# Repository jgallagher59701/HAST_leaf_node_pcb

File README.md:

# HAST leaf node pcb files

The first PCB used EagleCAD, but I've switched to KiCAD. Version 0.5 is the current version of the PCB in used as of Nov. 2021.

Supportted by a grant from ESIP.

Contact: jgallagher@opendap.org

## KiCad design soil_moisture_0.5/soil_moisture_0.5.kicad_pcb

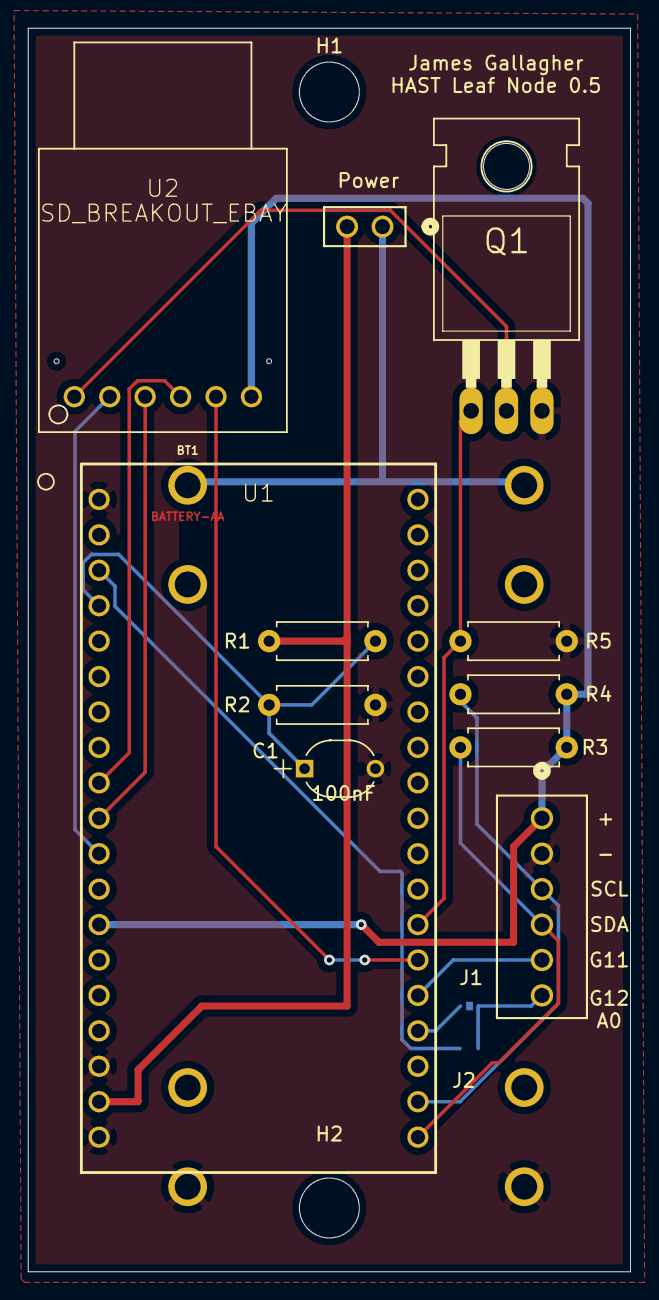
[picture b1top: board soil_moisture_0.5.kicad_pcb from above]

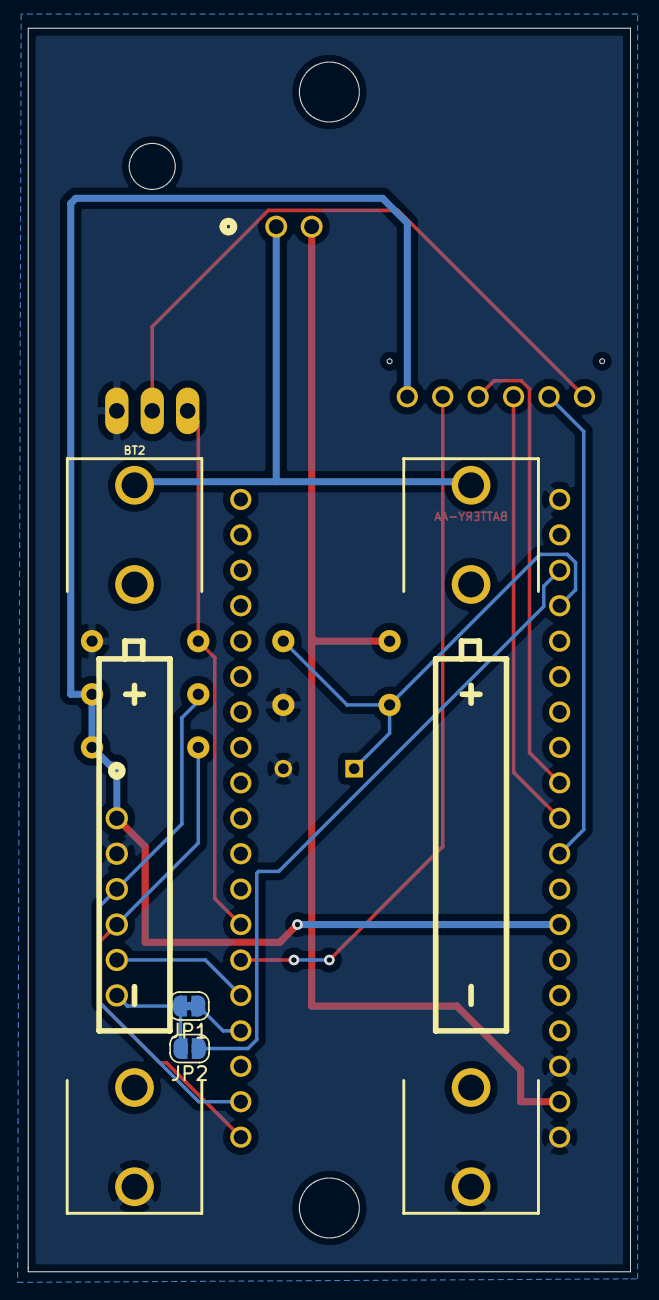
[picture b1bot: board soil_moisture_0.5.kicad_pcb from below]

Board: 2 copper layers, 43.2 x 89.2 mm, 17 parts (4 on the bottom side), 17 nets.

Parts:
BT1, BT2: BATTERY-AA; BATTERY-AA-KIT
C1: 100nF; C322C104K5R5TA
H1, H2: MountingHole; MountingHole_4.3mm_M4
J1: PPTC021LFBN-RC; CONN2_LFBN-RC_SUL
J2: 1725698; CONN_1725698_PXC
JP1: SolderJumper_2_Bridged; SolderJumper-2_P1.3mm_Bridged_RoundedPad1.0x1.5mm
JP2: SolderJumper_2_Open; SolderJumper-2_P1.3mm_Open_RoundedPad1.0x1.5mm
Q1: FDP7030BL; TO220
R1, R2: 1M; R_Axial_DIN0207_L6.3mm_D2.5mm_P7.62mm_Horizontal
R3, R4, R5: 10k; R_Axial_DIN0207_L6.3mm_D2.5mm_P7.62mm_Horizontal
U1: RS_MINI_ULTRA_PRO_V3; RS_MINI_ULTRA_PRO_V2
U2: SD_BREAKOUT_EBAY

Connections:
3V3: J2.1, R3.2, R4.2, U1.13, U2.3V3
A0: JP2.1, U1.3
BAT: J1.2, R1.1, U1.18
GND: BT1.GND@1, BT2.GND@1, C1.2, J2.2, Q1.3, R2.2, R5.2, U1.1, U1.17, U1.19
GPIO11: J2.5, U1.24
GPIO12: JP1.1, U1.23
MISO: U1.11, U2.MISO
MOSI: U1.9, U2.MOSI
unnamed: BT1.PWR@1, BT2.PWR@1, J1.1
unnamed: C1.1, R1.2, R2.1, U1.4
unnamed: J2.6, JP1.2, JP2.2
unnamed: Q1.1, R5.1, U1.26
unnamed: Q1.2, U2.GND
SCK: U1.10, U2.CLK
SCL: J2.3, R4.1, U1.21
SDA: J2.4, R3.1, U1.20
SS: U1.25, U2.CS

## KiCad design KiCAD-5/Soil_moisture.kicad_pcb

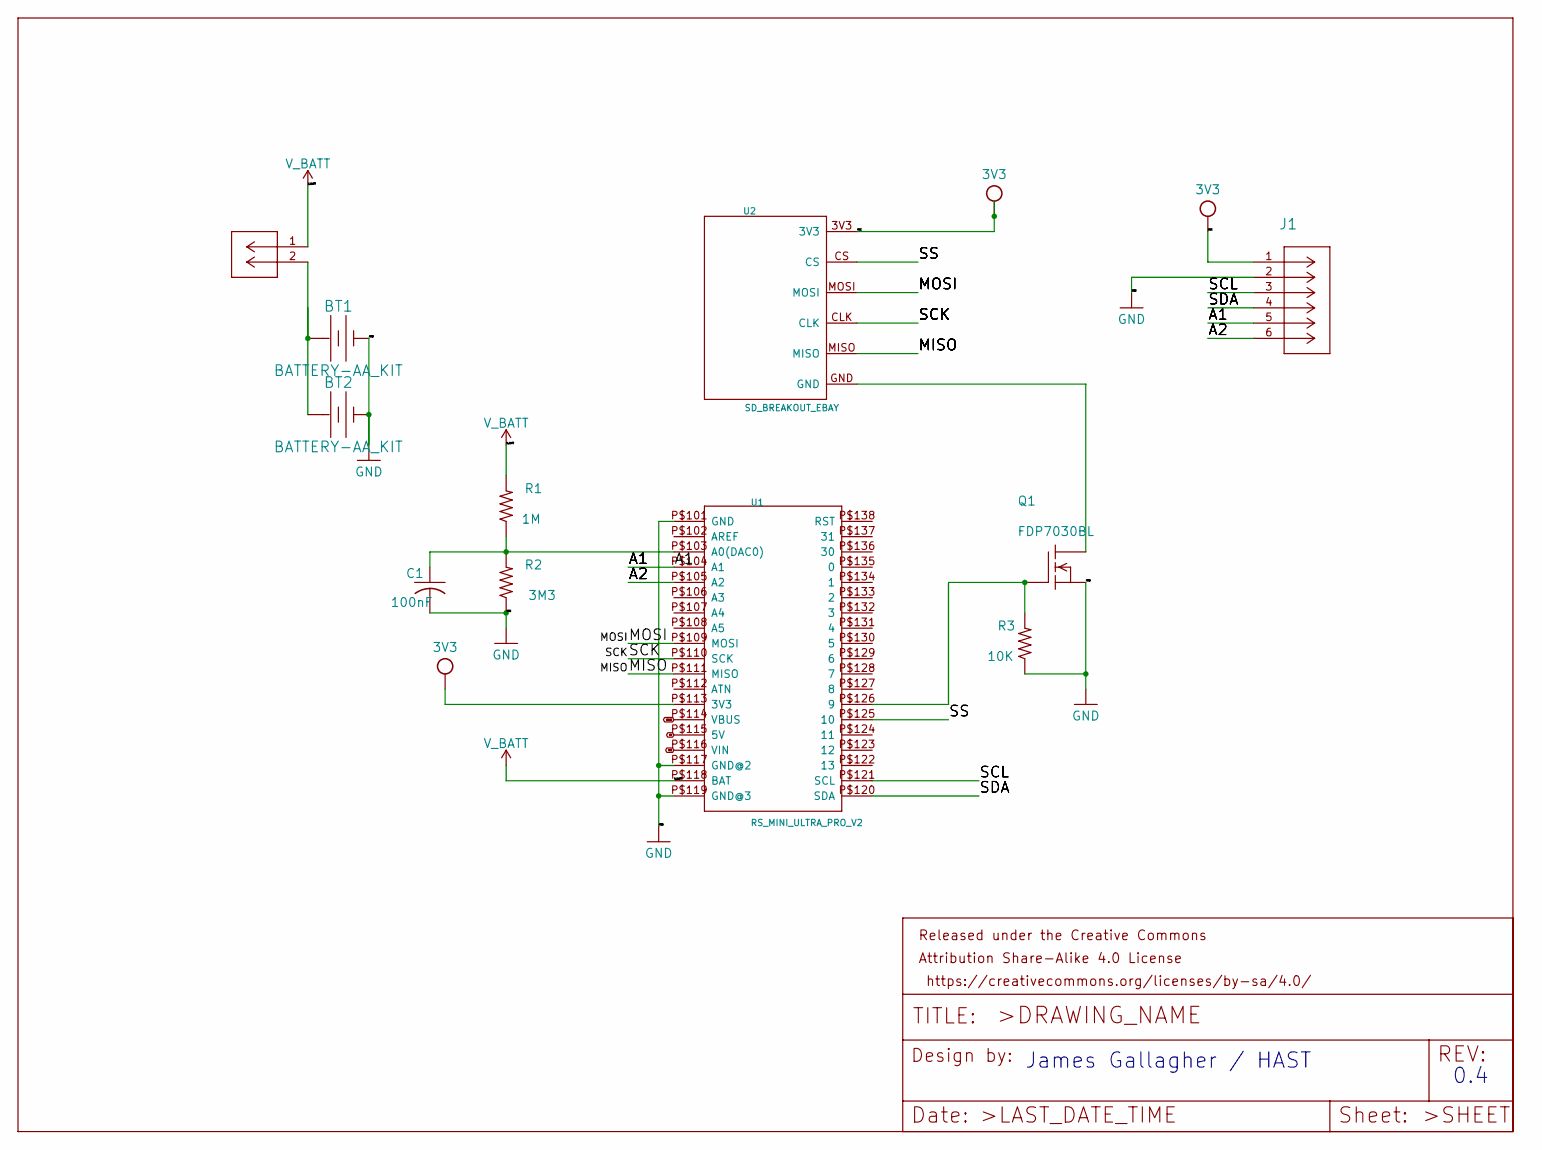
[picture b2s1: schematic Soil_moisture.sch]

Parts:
BAT_GND1: PPTC021LFBN-RC; CONN2_LFBN-RC_SUL
BT1, BT2: BATTERY-AA_KIT; BATTERY-AA-KIT
C1: 100nF; C050-035X075
FRAME1: FRAME-LETTER; CREATIVE_COMMONS
J1: 1725698; CONN_1725698_PXC
Q1: FDP7030BL; TO220
R1: 1M; 0309_10
R2: 3M3; 0309_10
R3: 10K; 0309_10
U1: RS_MINI_ULTRA_PRO_V2
U2: SD_BREAKOUT_EBAY

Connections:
5V: U1.P$115 (5V)
/A1: J1.5, U1.P$104 (A1)
/A2: J1.6, U1.P$105 (A2)
/MISO: U1.P$111 (MISO), U2.MISO
/MOSI: U1.P$109 (MOSI), U2.MOSI
/SCK: U1.P$110 (SCK), U2.CLK
/SCL: J1.3, U1.P$121 (SCL)
/SDA: J1.4, U1.P$120 (SDA)
/SS: U1.P$125 (10), U2.CS
GND: BT1.GND@1 (-), BT2.GND@1 (-), C1.2, J1.2, Q1.3 (S), R2.1, R3.1, U1.P$101 (GND), U1.P$117 (GND@2), U1.P$119 (GND@3)
unnamed: BAT_GND1.2, BT1.PWR@1 (+), BT2.PWR@1 (+)
unnamed: C1.1, R1.1, R2.2, U1.P$103 (A0(DAC0))
unnamed: Q1.1 (G), R3.2, U1.P$126 (9)
unnamed: Q1.2 (D), U2.GND
VBUS: U1.P$114 (VBUS)
VCC: J1.1, U1.P$113 (3V3), U2.3V3
VIN: U1.P$116 (VIN)
V_BATT: BAT_GND1.1, R1.2, U1.P$118 (BAT)

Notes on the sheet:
James Gallagher / HAST
0.4

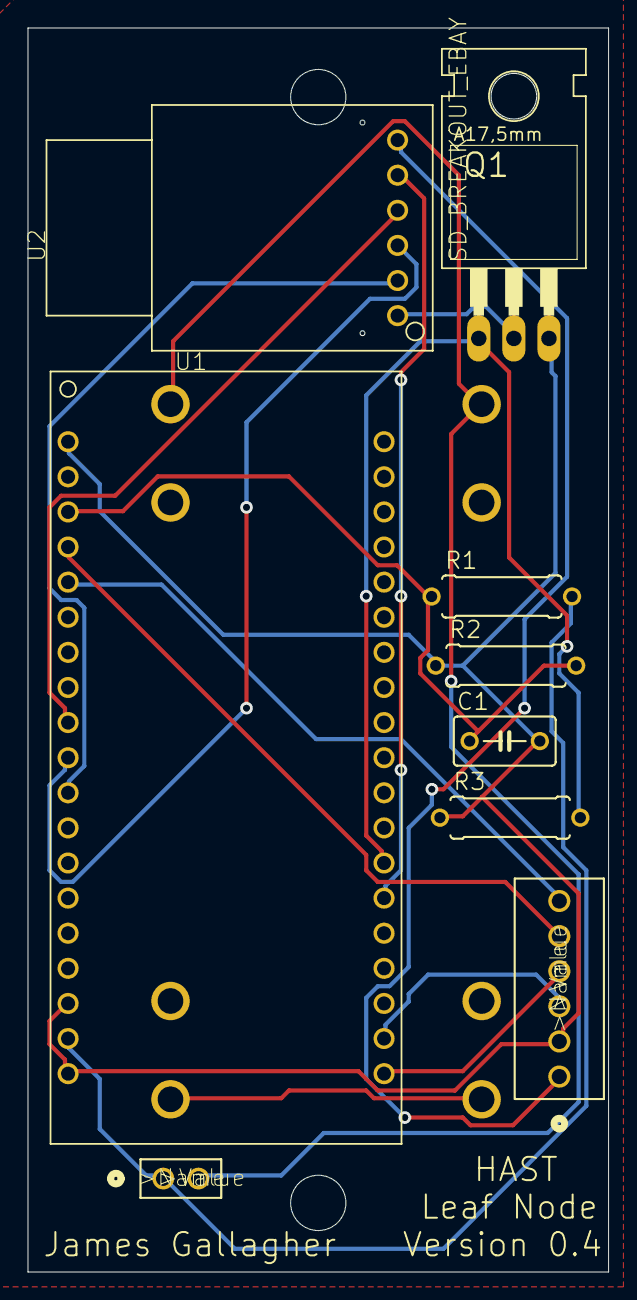
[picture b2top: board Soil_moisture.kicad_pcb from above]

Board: 2 copper layers, 42.0 x 90.0 mm, 14 parts (0 on the bottom side), 15 nets.

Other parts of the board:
@HOLE0, @HOLE1: (no value)

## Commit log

2021-03-10 Imported Eagle schematic to KiCAD, added the result here.
2021-03-10 Added a note about KiCAD 5 to the README
2021-08-27 PCB version 0.5 - now with 3D models
2021-08-28 Various hacks - added jumpers for GPIO/A0
2021-09-07 Added second voltage divider for Vbat; board outline
2021-09-09 Added Gerbers and a BOM
2021-09-13 BOM updates
2021-10-01 Added a PDF of the schematic
2021-10-01 At the office, KiCAD is using newer libraries.
    This is an update based on those newer libraries. I may
    have to update KiCAD at home to use the files on this branch.
    Test, merge if possible.
2021-11-18 Cache update
    Not sure this should be in git, but it is...

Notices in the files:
soil_moisture_0.5/soil_moisture_0.5.kicad_pcb:
License: CC BY 4.0
parts and their libraries:
https://creativecommons.org/licenses/by-sa/4.0
Released under the Creative Commons Attribution Share-Alike 4.0 License
my_library: COPYRIGHT: Copyright (C) 2018 Accelerated Designs. All rights reserved
SparkFun-Aesthetics: Released under the Creative Commons
